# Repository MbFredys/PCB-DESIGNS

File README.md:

<h1>PCB Designs for PLATZI course</h1>

This repository contains the projects I completed during the Platzi course on PCB design. These projects are exactly as I left them at the end of the course, despite any errors I may have made in the designs (LOL). It was an excellent basic course that helped me learn the fundamentals of PCB design.

<h1>Projects</h1>

The following are the projects included in this repository:

1. Small Power Supply
2. Development Board (like Arduino Uno but better)

<h1>Course Information</h1>

If you are interested in learning PCB design, I highly recommend taking the Platzi course on [Circuitos Electrónicos ↗](https://platzi.com/cursos/circuitos-electronicos/). This course covers all the basics of PCB design and provides hands-on experience with projects.

<h1>🚀 Getting Started</h1>

To get started with these projects, simply clone this repository and open the project files in your preferred PCB design software. You can then modify and customize the designs as you see fit.

<h1>🤝 Contributing</h1>

Contributions are always welcome! If you have any suggestions for improving these projects or would like to add your own, feel free to open a pull request.

<h1>📝 License</h1>

These projects are licensed under the [MIT License ↗](https://opensource.org/license/mit/). Feel free to use them for any purpose, commercial or non-commercial.

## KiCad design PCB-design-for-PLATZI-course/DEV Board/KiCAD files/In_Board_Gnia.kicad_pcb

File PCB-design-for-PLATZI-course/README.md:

These are the projects I completed during the Platzi course. They are just as I left them at the end of the course, despite any errors I may have made in the designs (LOL). It was an excellent basic course. 

If you are interested, here is the link: https://platzi.com/cursos/circuitos-electronicos/

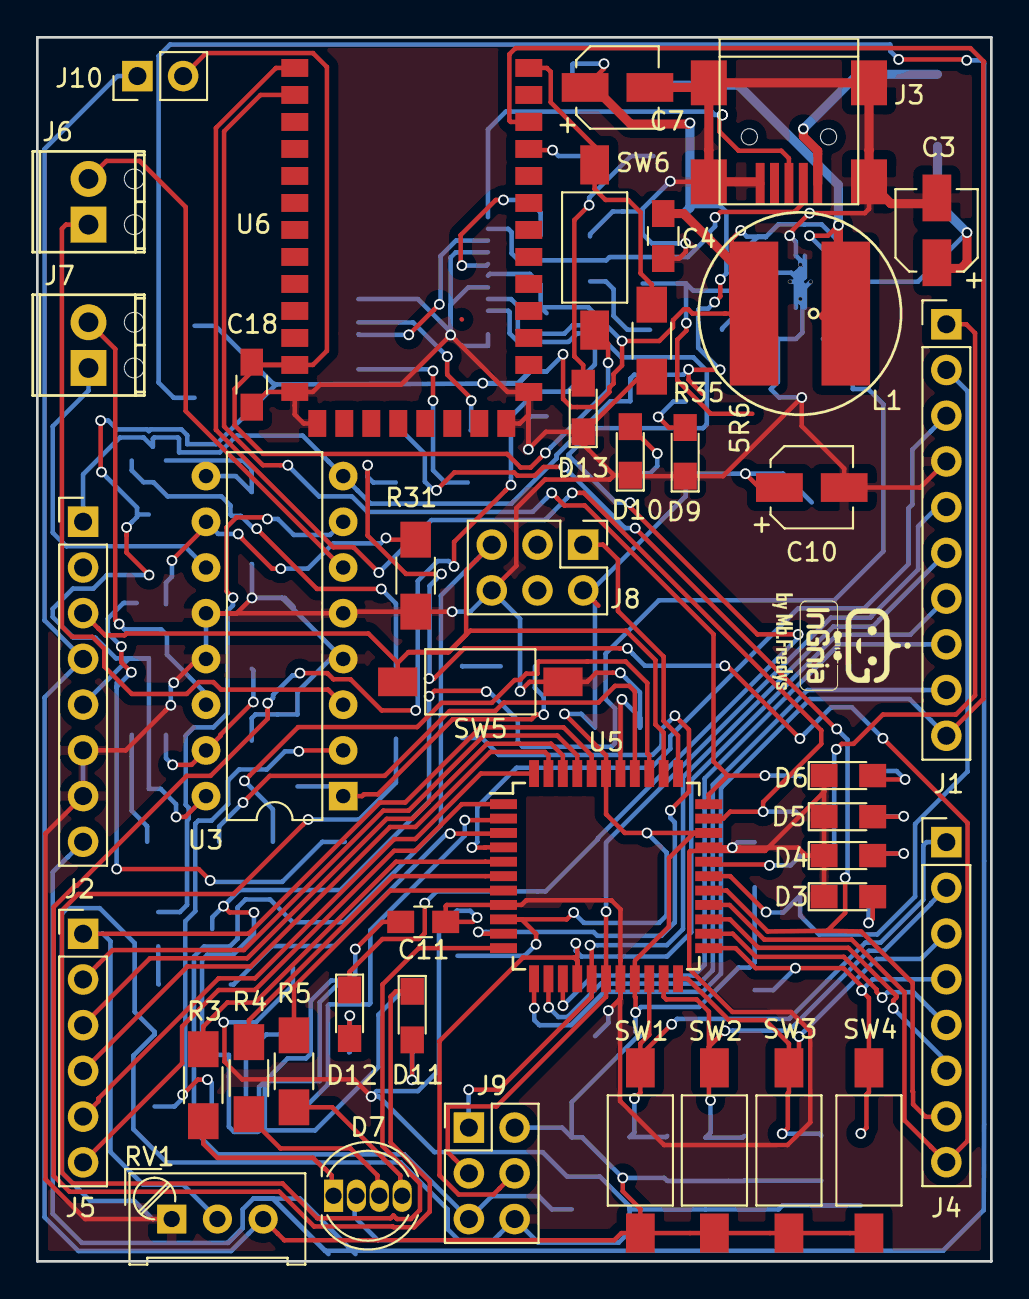
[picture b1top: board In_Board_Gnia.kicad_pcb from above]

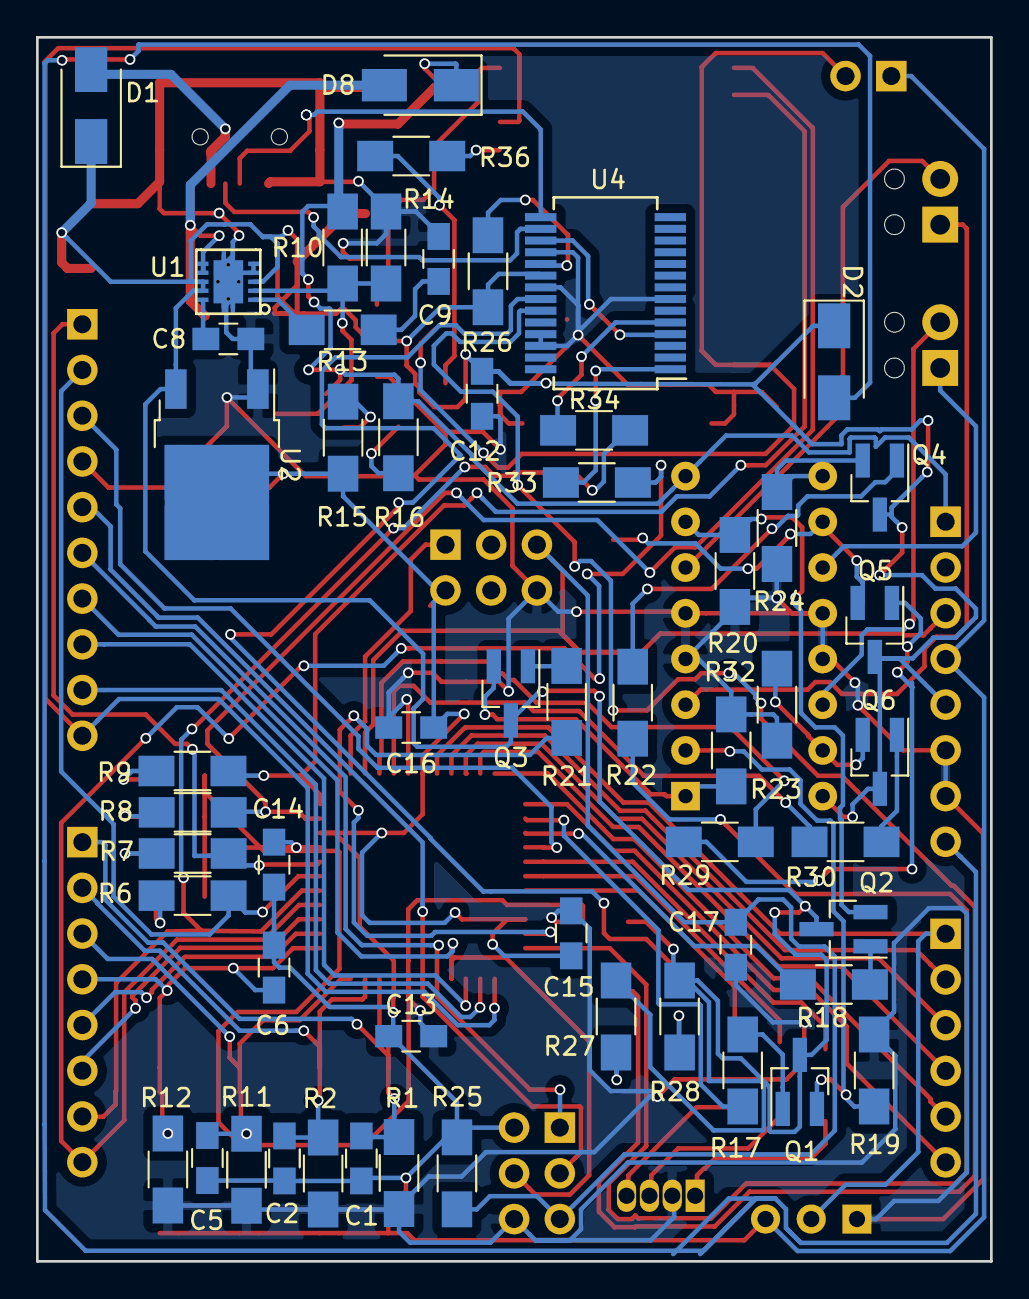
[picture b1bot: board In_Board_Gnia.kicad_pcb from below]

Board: 2 copper layers, 53.0 x 68.0 mm, 97 parts (55 on the bottom side), 86 nets.

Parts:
C1, C2, C5, C6, C8, C11, C12, C13, C14, C15, C16, C17, C18: 100nF; C_0805_HandSoldering
C3, C10: 10uF; CP_Elec_4x4.5
C4: 1uF; C_0805_HandSoldering
C7: 22uF; CP_Elec_4x5.3
C9: 820pF; C_0805_HandSoldering
D1, D2: D_Schottky; D_SMA
D3, D4, D5, D6, D9, D10, D11, D12, D13: LED; LED_0805_HandSoldering
D7: LED_RCGB; LED_D5.0mm-4
D8: B340A-13-F; D_SMA
J1: Conn_01x10; Pin_Header_Straight_1x10_Pitch2.54mm
J2, J4: Conn_01x08; Pin_Header_Straight_1x08_Pitch2.54mm
J3: USB_OTG; USB_Mini-B
J5: Conn_01x06; Pin_Header_Straight_1x06_Pitch2.54mm
J6, J7: Conn_01x02; TerminalBlock_Phoenix_MPT-2.54mm_2pol
J8, J9: Conn_02x03_Odd_Even; Pin_Header_Straight_2x03_Pitch2.54mm
J10: Conn_01x02; Pin_Header_Straight_1x02_Pitch2.54mm
L1: 5.6uH; SDR0805
Q1, Q2, Q3, Q4, Q5, Q6: MMBT3904; SOT-23_Handsoldering
R1, R2, R11, R12, R19, R20, R23, R24, R25, R26, R31, R32, R35: 10K; R_1206_HandSoldering
R3, R4, R5, R6, R7, R8, R9, R15, R16, R27, R28: 330; R_1206_HandSoldering
R10: 232K; R_1206_HandSoldering
R13: 105K; R_1206_HandSoldering
R14: 26.7K; R_1206_HandSoldering
R17, R18, R21, R22, R29, R30, R33, R34: 1K; R_1206_HandSoldering
R36: 2K; R_1206_HandSoldering
RV1: R_POT_TRIM; Potentiometer_Trimmer_Bourns_PV36W
SW1, SW2, SW3, SW4, SW5, SW6: SW_Push; SW_SPST_FSMSM
U1: TPS61087DSCR; TPS61087
U2: LM1117-3.3; TO-252-2
U3: L293D; DIP-16_W7.62mm
U4: FT232RL; SSOP-28_5.3x10.2mm_Pitch0.65mm
U5: ATXMEGA32A4U-AU; TQFP-44_10x10mm_Pitch0.8mm
U6: HC-05

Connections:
+3.3VP: C18.1, J10.2, SW6.2, U6.12
+3V3: C1.1, C2.1, C5.1, C6.1, C10.1, C13.1, C14.1, C15.1, C16.1, J2.4, J8.2, J9.2, J10.1, R15.2, R25.2, RV1.3, SW1.2, SW2.2, SW3.2, SW4.2, U2.2, U5.9, U5.19, U5.31, U5.39
+5V: C3.1, C4.1, C11.1, C12.1, D1.1, D2.1, J2.5, L1.2, Q1.3, Q2.3, Q3.3, Q4.3, Q5.3, Q6.3, R26.2, R27.2, R28.2, U1.3, U1.8, U1.9, U2.3, U3.16, U4.20
+12V: C7.1, D8.1, J2.1, R10.1, R16.2, U3.8
/1A: Q1.2, R19.2, U3.2
/2A: Q2.2, R20.2, U3.7
/3A: Q5.2, R31.2, U3.10
/4A: Q6.2, R32.2, U3.15
/A0: J5.1, RV1.2, U5.40
/A1: J5.2, U5.41
/A2: J5.3, U5.42
/A3: J5.4, U5.43
/A4: J5.5, U5.44
/A5: J5.6, U5.1
/AREF: J1.3, U5.4
/BT_RX: R9.2, U5.33, U6.2
/BT_STATE: J1.10, U5.12, U6.32
/BT_TX: R8.2, U5.32, U6.1
/D+: J3.3, U4.15
/D-: J3.2, U4.16
/EN1,2: Q3.2, R23.2, U3.1
/EN3,4: Q4.2, R24.2, U3.9
/FB: R10.2, R14.1, U1.2
/LED1: J1.2, R6.2, U5.28
/LED2: J1.1, R7.2, U5.29
/LED_B: R5.2, U5.7
/LED_G: R4.2, U5.6
/LED_R: R3.2, U5.5
/MISO: J1.6, J9.1, U5.16
/MOSI: J1.7, J9.4, U5.15
/MOT1_A: R17.1, U5.2
/MOT1_B: R18.1, U5.3
/MOT1_PWM: R21.1, U5.10
/MOT2_A: R29.1, U5.36
/MOT2_B: R30.1, U5.37
/MOT2_PWM: R22.1, U5.11
/PD0: C1.2, J4.1, R1.2, SW1.1, U5.20
/PD1: C2.2, J4.2, R2.2, SW2.1, U5.21
/PD2: C5.2, J4.3, R11.2, SW3.1, U5.22
/PD3: C6.2, J4.4, R12.2, SW4.1, U5.23
/PD4: J4.5, U5.24
/PD5: J4.6, U5.25
/PDI_DATA: J8.1, U5.34
/PWM: J1.9, U5.13
/PWM/CS: J1.8, U5.14
/RESET: C17.1, J2.3, J8.5, J9.5, R25.1, SW5.2, U5.35
/RXD: R34.1, U4.5
/RXD1: J4.8, R33.2, U5.26
/SCK: J1.5, J9.3, U5.17
/TXD: R33.1, U4.1
/TXD1: J4.7, R34.2, U5.27
/VIN: D2.2, J2.8
GND: C3.2, C4.2, C7.2, C8.2, C9.2, C10.2, C11.2, C12.2, C13.2, C14.2, C15.2, C16.2, C17.2, C18.2, D3.1, D4.1, D5.1, D6.1, D7.2, D9.1, D10.1, D13.1, J1.4, J2.6, J2.7, J3.5, J3.6, J8.6, J9.6, R1.1, R2.1, R11.1, R12.1, R14.2, R19.1, R20.1, R23.1, R24.1, R31.1, R32.1, R35.2, RV1.1, SW5.1, U1.4, U1.5, U1.11, U2.1, U3.4, U3.5, U3.12, U3.13, U4.7, U4.18, U4.21, U4.25, U4.26, U5.8, U5.18, U5.30, U5.38, U6.13, U6.14, U6.21, U6.22
unnamed: C8.1, U1.10
unnamed: C9.1, R13.2
unnamed: D3.2, R6.1
unnamed: D4.2, R7.1
unnamed: D5.2, R8.1
unnamed: D6.2, R9.1
unnamed: D7.1, R3.1
unnamed: D7.3, R4.1
unnamed: D7.4, R5.1
unnamed: D8.2, L1.1, U1.6, U1.7
unnamed: D9.2, R15.1
unnamed: D10.2, R16.1
unnamed: D11.1, U4.23
unnamed: D11.2, R27.1
unnamed: D12.1, U4.22
unnamed: D12.2, R28.1
unnamed: D13.2, R36.2
unnamed: J6.1, U3.3
unnamed: J6.2, U3.6
unnamed: J7.1, U3.11
unnamed: J7.2, U3.14
unnamed: Q1.1, R17.2
unnamed: Q2.1, R18.2
unnamed: Q3.1, R21.2
unnamed: Q4.1, R22.2
unnamed: Q5.1, R29.2
unnamed: Q6.1, R30.2
unnamed: R13.1, U1.1
unnamed: R26.1, U4.19
unnamed: R35.1, SW6.1, U6.34
unnamed: R36.1, U6.31
unnamed: U4.4, U4.17
VBUS: D1.2, J3.1

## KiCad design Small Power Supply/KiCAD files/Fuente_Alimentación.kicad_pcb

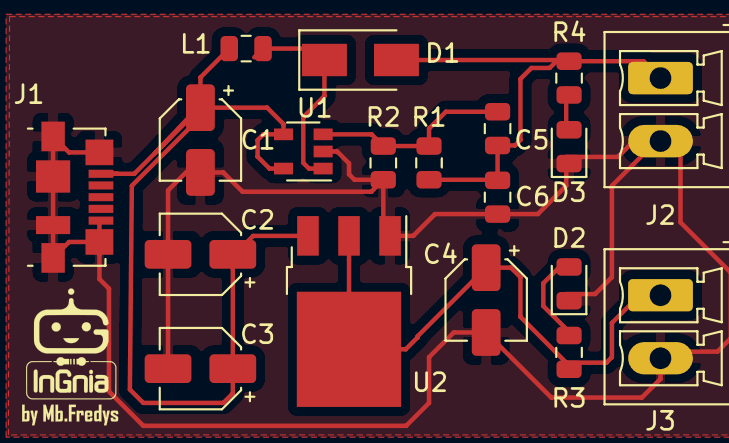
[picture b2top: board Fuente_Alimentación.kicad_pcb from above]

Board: 2 copper layers, 19 parts (0 on the bottom side), 8 nets.

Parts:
C1: 4.7uF; CP_Elec_4x4.5
C2, C4: 10uF; CP_Elec_4x4.5
C3: 1uF; CP_Elec_4x4.5
C5: 2 pF; C_0805_2012Metric
C6: 4.7pF; C_0805_2012Metric
D1: MBRM120L; D_SMA
D2, D3: LED; LED_0805_2012Metric
J1: USB_OTG; USB_Micro-B_Molex_47346-0001
J2, J3: Conn_01x02; PhoenixContact_MCV_1,5_2-G-3.5_1x02_P3.50mm_Vertical
L1: 10uH; L_0805_2012Metric
R1: 1.8M; R_0805_2012Metric
R2: 200K; R_0805_2012Metric
R3, R4: 330; R_0805_2012Metric
U1: TPS61041DBV; SOT-23-5
U2: LM1117-3.3; TO-252-3_TabPin2

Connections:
+3V3: C4.1, J3.1, R3.1, U2.2
+5V: C1.1, C2.1, C3.1, J1.1, L1.1, U1.4, U1.5, U2.3
+12V: C5.1, C6.1, D1.2, J2.1, R1.1, R4.1
GND: C1.2, C2.2, C3.2, C4.2, C6.2, D2.1, D3.1, J1.5, J1.6, J2.2, J3.2, R2.2, U1.2, U2.1
unnamed: C5.2, R1.2, R2.1, U1.3
unnamed: D1.1, L1.2, U1.1
unnamed: D2.2, R3.2
unnamed: D3.2, R4.2

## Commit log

2023-05-30 Create PDF Schematics
2023-05-30 Temperature Controller
2023-05-30 Create PDF KiCAD Schematics
2023-05-30 Create Manufacturing
2023-05-30 Create Release
2023-05-30 Create Temp-controller
2023-05-30 Create firmware
2023-05-30 Create schematics
2023-05-30 Create power-supply
2023-05-30 Update schematics
2023-05-30 Update PDF KiCAD Schematics
2023-06-14 Rename Temp-controller to Temp-controller.md
2023-06-14 Modificando el Repo
2023-06-15 Agregando KiCAD files
2023-06-23 Modificando estructura del repo
2023-06-23 Agregando el CONTROLADOR DE TEMPERATURA al repo
2023-06-23 Rename Temp-controller.md to README.md
2023-06-23 Rename dev-board.md to README.md
2023-06-23 Rename power-supply to README.md
2023-07-12 agregando nuevo proyecto , el controlador LED
2023-07-12 Agregando PROYECTO NUEVO led controller
2023-07-16 Editando archivos del repositorio
